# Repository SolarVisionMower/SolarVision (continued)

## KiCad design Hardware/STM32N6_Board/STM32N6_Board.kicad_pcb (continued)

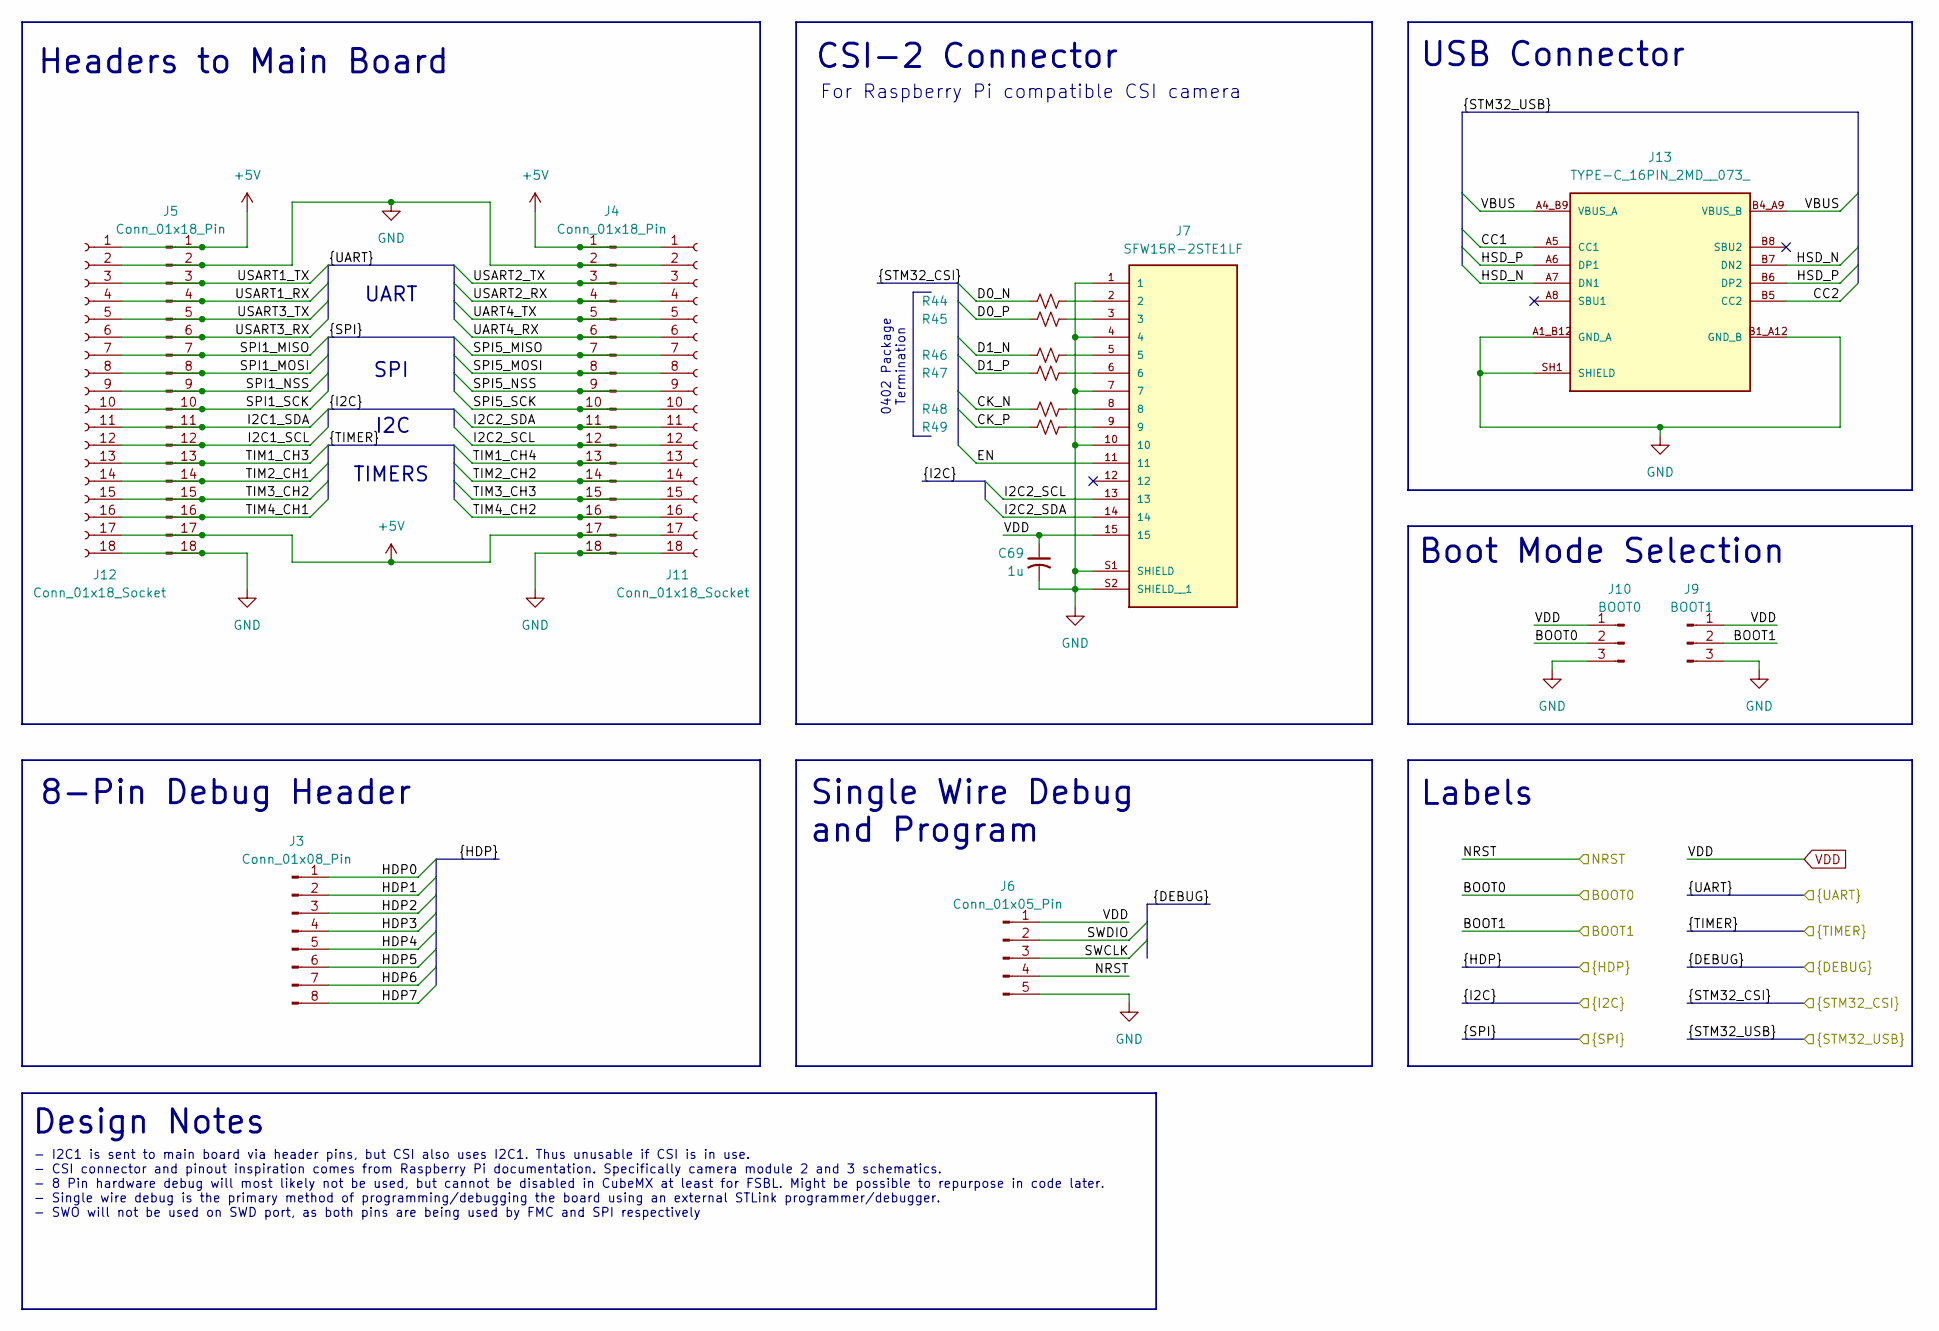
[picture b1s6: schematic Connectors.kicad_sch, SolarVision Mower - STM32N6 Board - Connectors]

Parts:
C69: 1u; C_0805_2012Metric_Pad1.18x1.45mm_HandSolder
J3: Conn_01x08_Pin; PinHeader_1x08_P2.54mm_Vertical
J4, J5: Conn_01x18_Pin; PinHeader_1x18_P2.54mm_Vertical
J6: Conn_01x05_Pin; PinHeader_1x05_P2.54mm_Vertical
J7: SFW15R-2STE1LF; AMPHENOL_SFW15R-2STE1LF; PARTREV AE
J9: BOOT1; PinHeader_1x03_P2.54mm_Vertical
J10: BOOT0; PinHeader_1x03_P2.54mm_Vertical
J11, J12: Conn_01x18_Socket; PinSocket_1x18_P2.54mm_Vertical
J13: TYPE-C_16PIN_2MD__073_; SHOUHAN_TYPE-C_16PIN_2MD__073_; PARTREV A
R44, R45, R46, R47, R48, R49: 0R; R_0402_1005Metric

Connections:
+5V: J4.1, J4.17, J5.1, J5.17, J11.1, J11.17, J12.1, J12.17; also elsewhere on the board
/Analog_Unit/BOOT0: J10.2; also elsewhere on the board
/Analog_Unit/CC1: J13.A5 (CC1); also elsewhere on the board
/Analog_Unit/CC2: J13.B5 (CC2); also elsewhere on the board
/Analog_Unit/CK_N: R48.1; also elsewhere on the board
/Analog_Unit/CK_P: R49.1; also elsewhere on the board
/Analog_Unit/D0_N: R44.1; also elsewhere on the board
/Analog_Unit/D0_P: R45.1; also elsewhere on the board
/Analog_Unit/D1_N: R46.1; also elsewhere on the board
/Analog_Unit/D1_P: R47.1; also elsewhere on the board
/Analog_Unit/EN: J7.11; also elsewhere on the board
/Analog_Unit/HSD_N: J13.A7 (DN1), J13.B7 (DN2); also elsewhere on the board
/Analog_Unit/HSD_P: J13.A6 (DP1), J13.B6 (DP2); also elsewhere on the board
/Analog_Unit/NRST: J6.4; also elsewhere on the board
/Analog_Unit/VBUS: J13.A4_B9 (VBUS_A), J13.B4_A9 (VBUS_B); also elsewhere on the board
/Connectors/BOOT1: J9.2; also elsewhere on the board
/Connectors/HDP0: J3.1; also elsewhere on the board
/Connectors/HDP1: J3.2; also elsewhere on the board
/Connectors/HDP2: J3.3; also elsewhere on the board
/Connectors/HDP3: J3.4; also elsewhere on the board
/Connectors/HDP4: J3.5; also elsewhere on the board
/Connectors/HDP5: J3.6; also elsewhere on the board
/Connectors/HDP6: J3.7; also elsewhere on the board
/Connectors/HDP7: J3.8; also elsewhere on the board
/Connectors/I2C1_SCL: J5.12, J12.12; also elsewhere on the board
/Connectors/I2C1_SDA: J5.11, J12.11; also elsewhere on the board
/Connectors/I2C2_SCL: J4.12, J7.13, J11.12; also elsewhere on the board
/Connectors/I2C2_SDA: J4.11, J7.14, J11.11; also elsewhere on the board
/Connectors/SPI1_MISO: J5.7, J12.7; also elsewhere on the board
/Connectors/SPI1_MOSI: J5.8, J12.8; also elsewhere on the board
/Connectors/SPI1_NSS: J5.9, J12.9; also elsewhere on the board
/Connectors/SPI1_SCK: J5.10, J12.10; also elsewhere on the board
/Connectors/SPI5_MISO: J4.7, J11.7; also elsewhere on the board
/Connectors/SPI5_MOSI: J4.8, J11.8; also elsewhere on the board
/Connectors/SPI5_NSS: J4.9, J11.9; also elsewhere on the board
/Connectors/SPI5_SCK: J4.10, J11.10; also elsewhere on the board
/Connectors/SWCLK: J6.3; also elsewhere on the board
/Connectors/SWDIO: J6.2; also elsewhere on the board
/Connectors/TIM1_CH3: J5.13, J12.13; also elsewhere on the board
/Connectors/TIM1_CH4: J4.13, J11.13; also elsewhere on the board
/Connectors/TIM2_CH1: J5.14, J12.14; also elsewhere on the board
/Connectors/TIM2_CH2: J4.14, J11.14; also elsewhere on the board
/Connectors/TIM3_CH2: J5.15, J12.15; also elsewhere on the board
/Connectors/TIM3_CH3: J4.15, J11.15; also elsewhere on the board
/Connectors/TIM4_CH1: J5.16, J12.16; also elsewhere on the board
/Connectors/TIM4_CH2: J4.16, J11.16; also elsewhere on the board
/Connectors/UART4_RX: J4.6, J11.6; also elsewhere on the board
/Connectors/UART4_TX: J4.5, J11.5; also elsewhere on the board
/Connectors/USART1_RX: J5.4, J12.4; also elsewhere on the board
/Connectors/USART1_TX: J5.3, J12.3; also elsewhere on the board
/Connectors/USART2_RX: J4.4, J11.4; also elsewhere on the board
/Connectors/USART2_TX: J4.3, J11.3; also elsewhere on the board
/Connectors/USART3_RX: J5.6, J12.6; also elsewhere on the board
/Connectors/USART3_TX: J5.5, J12.5; also elsewhere on the board
GND: C69.2, J4.2, J4.18, J5.2, J5.18, J6.5, J7.1, J7.4, J7.7, J7.10, J7.S1 (SHIELD), J7.S2 (SHIELD__1), J9.3, J10.3, J11.2, J11.18, J12.2, J12.18, J13.A1_B12 (GND_A), J13.B1_A12 (GND_B), J13.SH1 (SHIELD), J13.SH2 (SHIELD), J13.SH3 (SHIELD), J13.SH4 (SHIELD); also elsewhere on the board
unnamed: J7.2, R44.2
unnamed: J7.3, R45.2
unnamed: J7.5, R46.2
unnamed: J7.6, R47.2
unnamed: J7.8, R48.2
unnamed: J7.9, R49.2
VDD: C69.1, J6.1, J7.15, J9.1, J10.1; also elsewhere on the board

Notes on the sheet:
Headers to Main Board
CSI-2 Connector
UART
- I2C1 is sent to main board via header pins, but CSI also uses I2C1. Thus unusable if CSI is in use. - CSI connector and pinout inspiration comes from Raspberry Pi documentation. Specifically camera module 2 and 3 schematics. - 8 Pin hardware debug will most likely not be used, but cannot be disab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
Design Notes
Boot Mode Selection
For Raspberry Pi compatible CSI camera
8-Pin Debug Header
SPI
USB Connector
TIMERS
Labels
I2C
0402 Package Termination
Single Wire Debug and Program

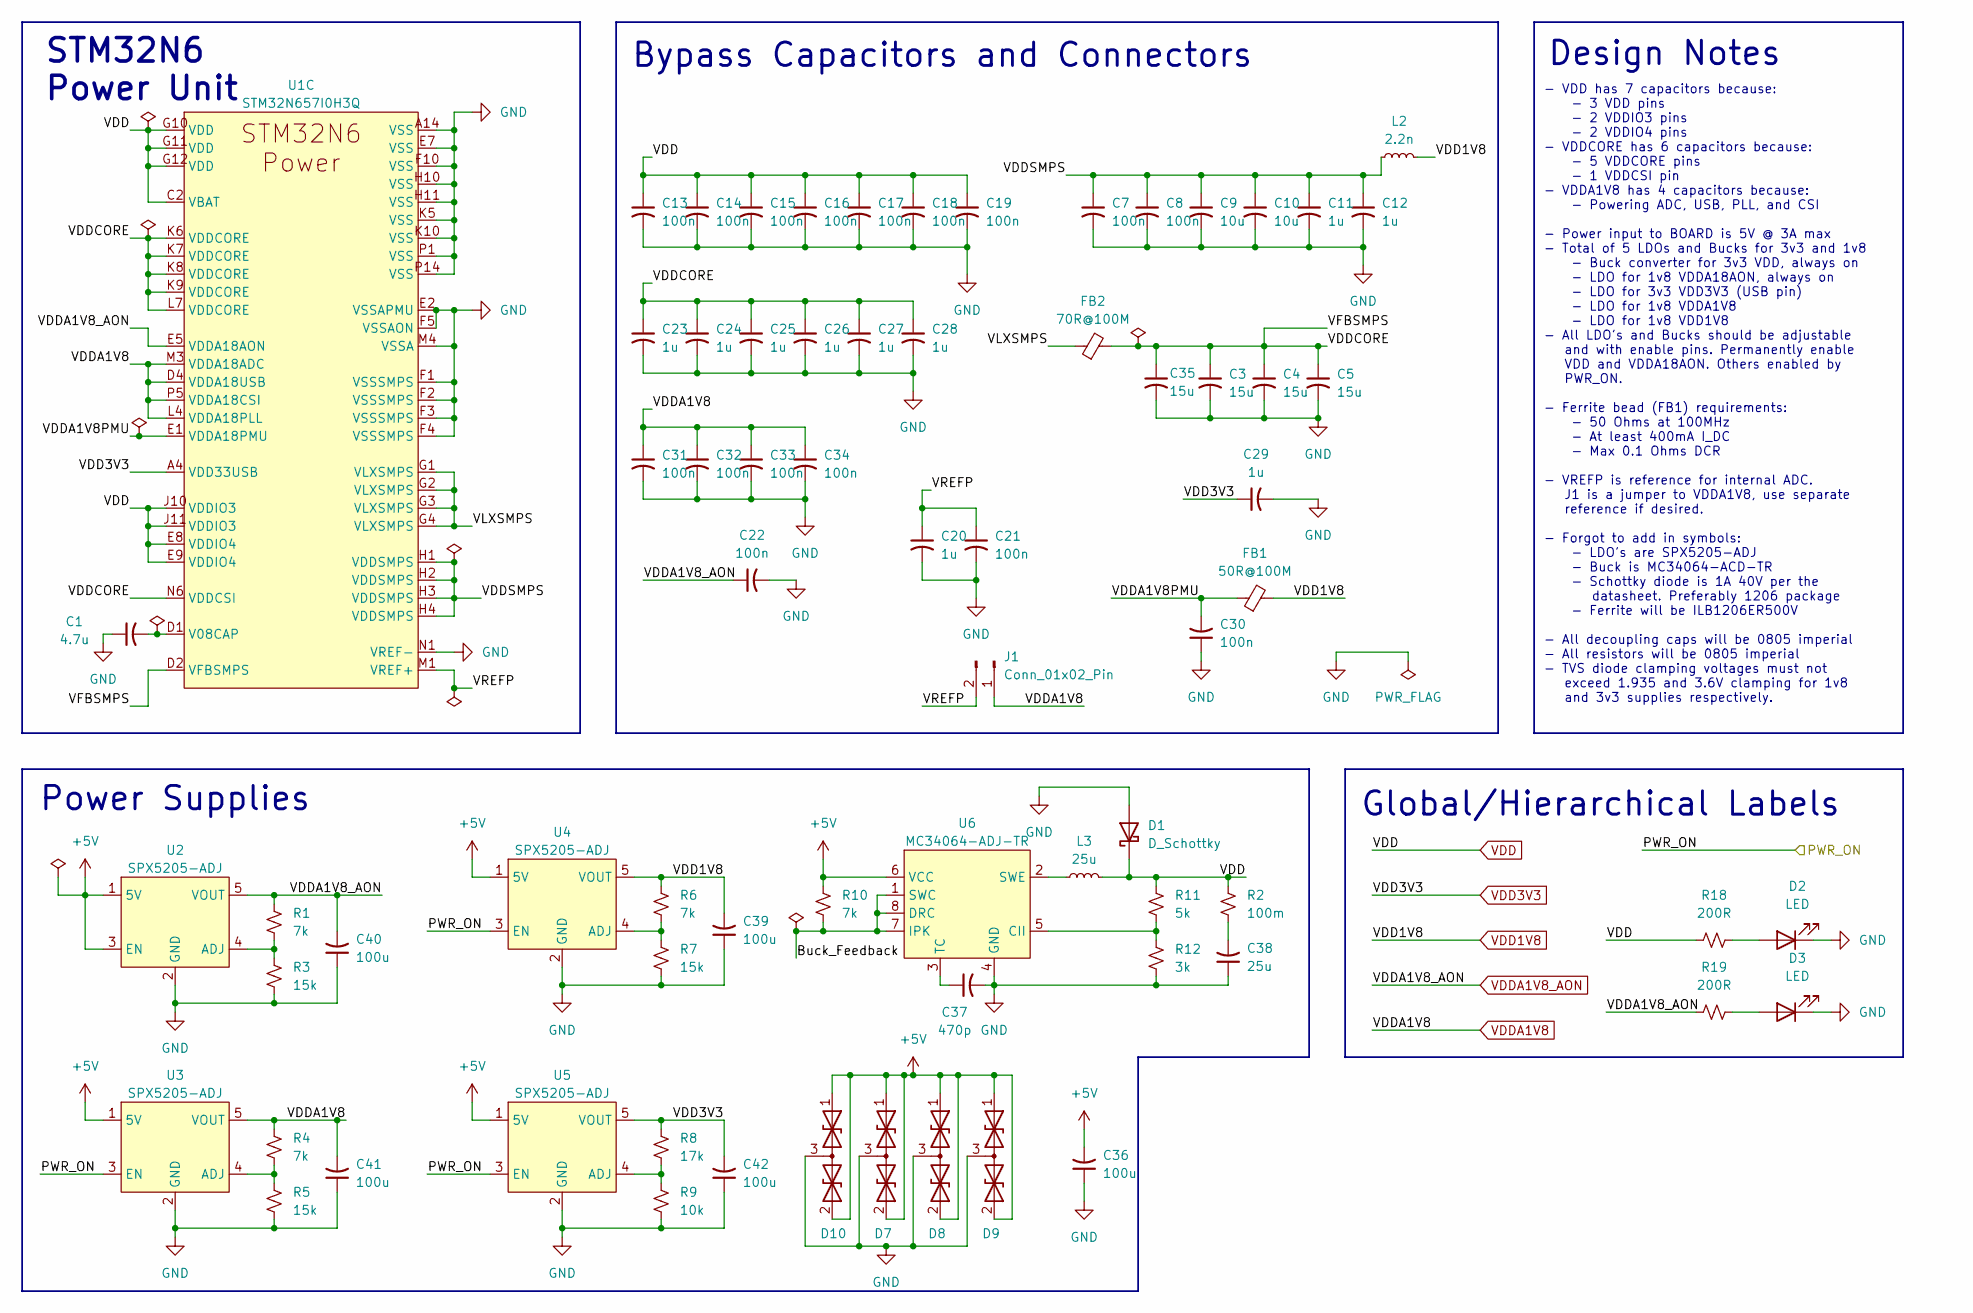
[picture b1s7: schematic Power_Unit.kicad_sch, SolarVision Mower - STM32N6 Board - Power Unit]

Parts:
C1: 4.7u; C_0402_1005Metric
C3, C4, C5, C35: 15u; C_0402_1005Metric
C7, C8, C13, C14, C15, C16, C17, C18, C19, C21, C22, C30, C31, C32, C33, C34: 100n; C_0402_1005Metric
C9, C10: 10u; C_0402_1005Metric
C11, C12, C20, C23, C24, C25, C26, C27, C28: 1u; C_0402_1005Metric
C29: 1u; C_0805_2012Metric_Pad1.18x1.45mm_HandSolder
C36, C39, C40, C41, C42: 100u; C_0805_2012Metric_Pad1.18x1.45mm_HandSolder
C37: 470p; C_0402_1005Metric
C38: 25u; C_0402_1005Metric
D1: D_Schottky; Schottky_DIOM4325X250N
D2, D3: LED; LED_0603_1608Metric_Pad1.05x0.95mm_HandSolder
D7, D8, D9, D10: D_TVS_Dual_AAC; SOT-723
FB1: 50R@100M; L_1206_3216Metric_Pad1.42x1.75mm_HandSolder
FB2: 70R@100M; L_1206_3216Metric_Pad1.42x1.75mm_HandSolder
J1: Conn_01x02_Pin; PinHeader_1x02_P2.54mm_Vertical
L2: 2.2n; L_1206_3216Metric_Pad1.42x1.75mm_HandSolder
L3: 25u; L_1206_3216Metric_Pad1.42x1.75mm_HandSolder
R1, R4, R6, R10: 7k; R_0805_2012Metric_Pad1.20x1.40mm_HandSolder
R2: 100m; R_0805_2012Metric_Pad1.20x1.40mm_HandSolder
R3, R5, R7: 15k; R_0805_2012Metric_Pad1.20x1.40mm_HandSolder
R8: 17k; R_0805_2012Metric_Pad1.20x1.40mm_HandSolder
R9: 10k; R_0805_2012Metric_Pad1.20x1.40mm_HandSolder
R11: 5k; R_0805_2012Metric_Pad1.20x1.40mm_HandSolder
R12: 3k; R_0805_2012Metric_Pad1.20x1.40mm_HandSolder
R18, R19: 200R; R_0402_1005Metric
U1: STM32N657I0H3Q; STM32N657I0H3Q_VFBGA178_14x14
U2, U3, U4, U5: SPX5205-ADJ; SOT-23-5
U6: MC34064-ADJ-TR; SO-8_3.9x4.9mm_P1.27mm

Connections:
+5V: C36.2, D7.1 (A1), D7.2 (A2), D8.1 (A1), D8.2 (A2), D9.1 (A1), D9.2 (A2), D10.1 (A1), D10.2 (A2), R10.1, U2.1 (5V), U2.3 (EN), U3.1 (5V), U4.1 (5V), U5.1 (5V), U6.6 (VCC); also elsewhere on the board
/Analog_Unit/PWR_ON: U3.3 (EN), U4.3 (EN), U5.3 (EN); also elsewhere on the board
/Power_Unit/Buck_Feedback: R10.2, U6.1 (SWC), U6.7 (IPK), U6.8 (DRC)
/Power_Unit/VDDA1V8PMU: C30.2, FB1.1, U1.E1 (VDDA18PMU)
/Power_Unit/VDDCORE: C3.1, C4.1, C5.1, C23.1, C24.1, C25.1, C26.1, C27.1, C28.1, C35.1, FB2.2, U1.D2 (VFBSMPS), U1.K6 (VDDCORE), U1.K7 (VDDCORE), U1.K8 (VDDCORE), U1.K9 (VDDCORE), U1.L7 (VDDCORE), U1.N6 (VDDCSI)
/Power_Unit/VDDSMPS: C7.1, C8.1, C9.1, C10.1, C11.1, C12.1, L2.1, U1.H1 (VDDSMPS), U1.H2 (VDDSMPS), U1.H3 (VDDSMPS), U1.H4 (VDDSMPS)
/Power_Unit/VLXSMPS: FB2.1, U1.G1 (VLXSMPS), U1.G2 (VLXSMPS), U1.G3 (VLXSMPS), U1.G4 (VLXSMPS)
/Power_Unit/VREFP: C20.1, C21.1, J1.2, U1.M1 (VREF+)
GND: C1.1, C3.2, C4.2, C5.2, C7.2, C8.2, C9.2, C10.2, C11.2, C12.2, C13.2, C14.2, C15.2, C16.2, C17.2, C18.2, C19.2, C20.2, C21.2, C22.2, C23.2, C24.2, C25.2, C26.2, C27.2, C28.2, C29.2, C30.1, C31.2, C32.2, C33.2, C34.2, C35.2, C36.1, C37.2, C38.1, C39.1, C40.1, C41.1, C42.1, D1.2 (A), D2.1 (K), D3.1 (K), D7.3 (common), D8.3 (common), D9.3 (common), D10.3 (common), R3.2, R5.2, R7.2, R9.2, R12.2, U1.A14 (VSS), U1.E2 (VSSAPMU), U1.E7 (VSS), U1.F1 (VSSSMPS), U1.F2 (VSSSMPS), U1.F3 (VSSSMPS), U1.F4 (VSSSMPS), U1.F5 (VSSAON), U1.F10 (VSS), U1.H10 (VSS), U1.H11 (VSS), U1.K5 (VSS), U1.K10 (VSS), U1.M4 (VSSA), U1.N1 (VREF-), U1.P1 (VSS), U1.P14 (VSS), U2.2 (GND), U3.2 (GND), U4.2 (GND), U5.2 (GND), U6.4 (GND); also elsewhere on the board
unnamed: D2.2 (A), R18.2
unnamed: D3.2 (A), R19.2
unnamed: C1.2, U1.D1 (V08CAP)
unnamed: R1.2, R3.1, U2.4 (ADJ)
unnamed: R4.2, R5.1, U3.4 (ADJ)
unnamed: R6.2, R7.1, U4.4 (ADJ)
unnamed: R8.2, R9.1, U5.4 (ADJ)
unnamed: R11.2, R12.1, U6.5 (CII)
unnamed: L3.1, U6.2 (SWE)
unnamed: C37.1, U6.3 (TC)
VDD: C13.1, C14.1, C15.1, C16.1, C17.1, C18.1, C19.1, C38.2, D1.1 (K), L3.2, R2.1, R2.2, R11.1, R18.1, U1.C2 (VBAT), U1.E8 (VDDIO4), U1.E9 (VDDIO4), U1.G10 (VDD), U1.G11 (VDD), U1.G12 (VDD), U1.J10 (VDDIO3), U1.J11 (VDDIO3); also elsewhere on the board
VDD1V8: C39.2, FB1.2, L2.2, R6.1, U4.5 (VOUT)
VDD3V3: C29.1, C42.2, R8.1, U1.A4 (VDD33USB), U5.5 (VOUT); also elsewhere on the board
VDDA1V8: C31.1, C32.1, C33.1, C34.1, C41.2, J1.1, R4.1, U1.D4 (VDDA18USB), U1.L4 (VDDA18PLL), U1.M3 (VDDA18ADC), U1.P5 (VDDA18CSI), U3.5 (VOUT)
VDDA1V8_AON: C22.1, C40.2, R1.1, R19.1, U1.E5 (VDDA18AON), U2.5 (VOUT); also elsewhere on the board

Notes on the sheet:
Global/Hierarchical Labels
Bypass Capacitors and Connectors
- VDD has 7 capacitors because: - 3 VDD pins - 2 VDDIO3 pins - 2 VDDIO4 pins - VDDCORE has 6 capacitors because: - 5 VDDCORE pins - 1 VDDCSI pin - VDDA1V8 has 4 capacitors because: - Powering ADC, USB, PLL, and CSI - Power input to BOARD is 5V @ 3A max - Total of 5 LDOs and Bucks for 3v3 and 1v8 - 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
Design Notes
STM32N6 Power Unit
Power Supplies

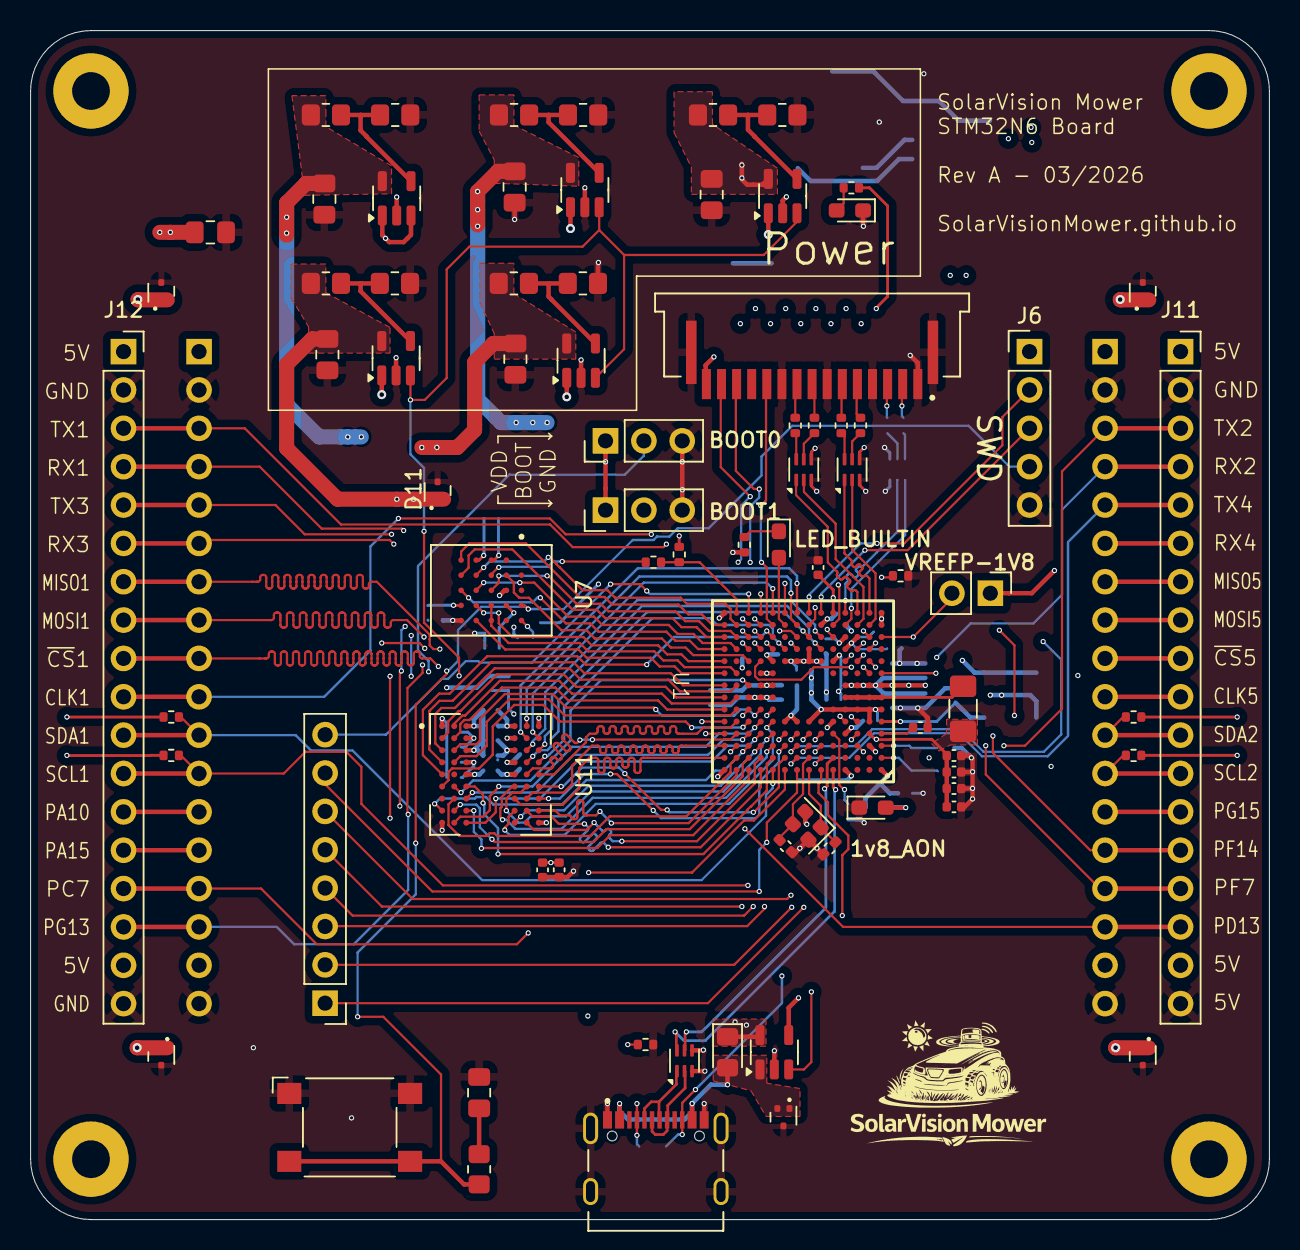
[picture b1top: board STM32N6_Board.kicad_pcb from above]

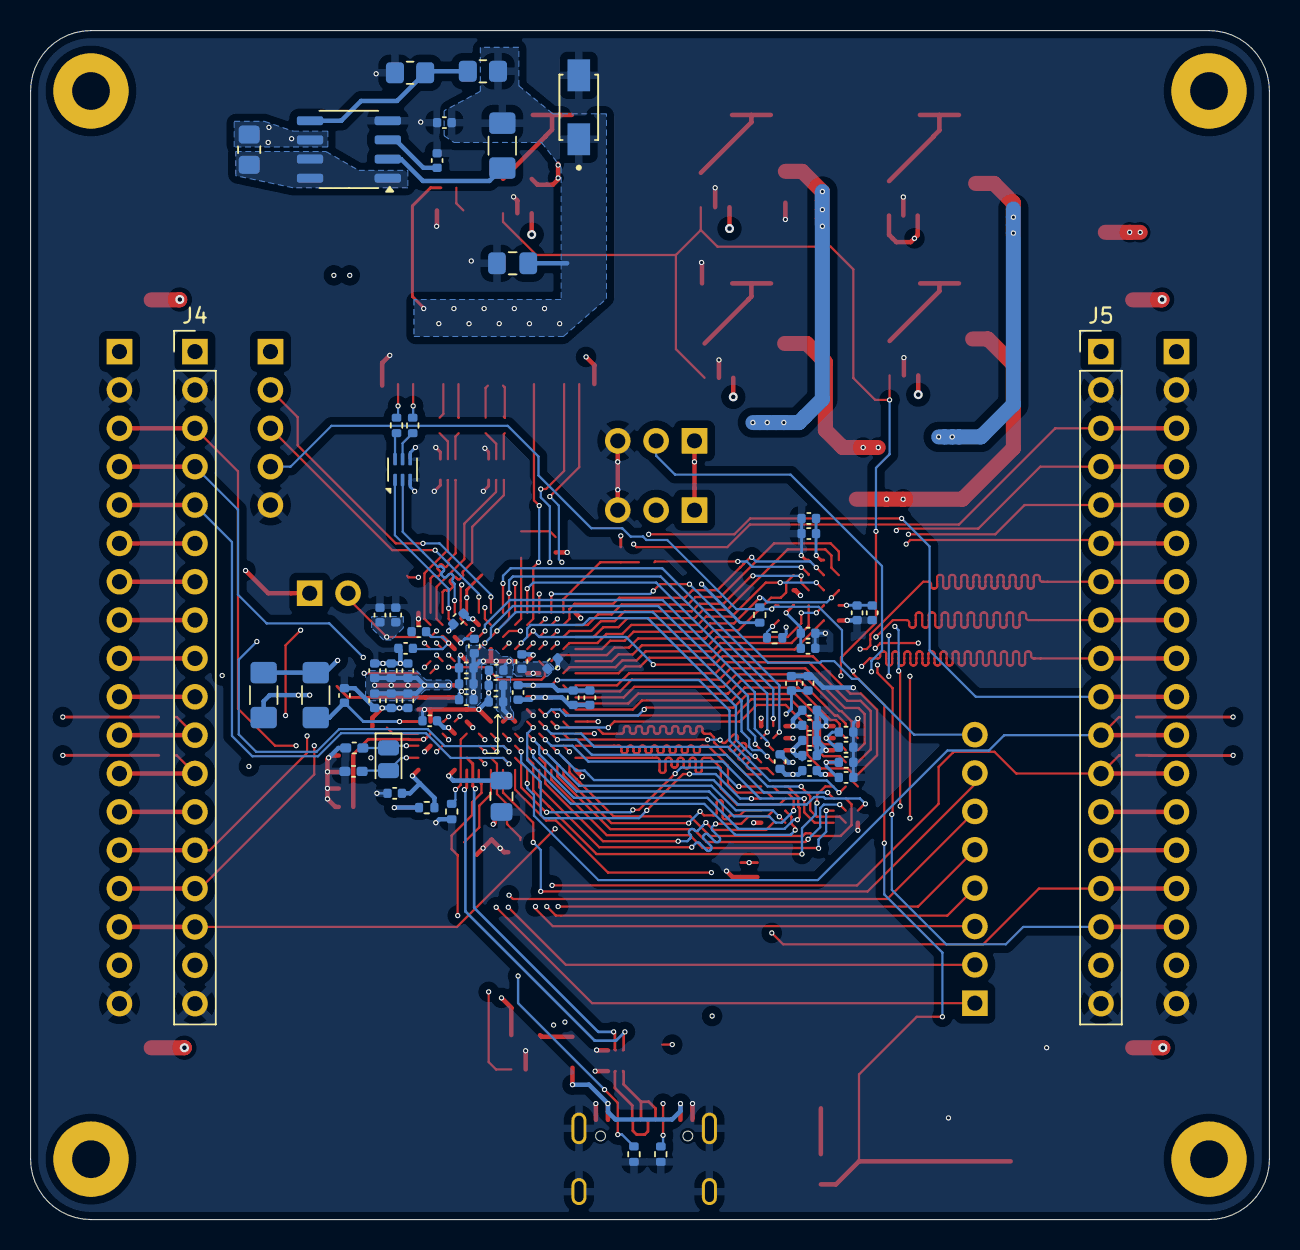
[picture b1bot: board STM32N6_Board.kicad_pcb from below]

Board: 6 copper layers, 82.0 x 78.7 mm, 146 parts (70 on the bottom side), 155 nets.

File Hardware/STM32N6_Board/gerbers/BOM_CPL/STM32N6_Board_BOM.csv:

"Id";"Designator";"Footprint";"Quantity";"Designation";"Supplier and ref";
1;"R31";"R_0402_1005Metric";1;"200";;;
2;"C42,C39,C41,C50,C40,C36";"C_0805_2012Metric_Pad1.18x1.45mm_HandSolder";6;"100u";;;
3;"U8,U2,U4,U5,U3";"SOT-23-5";5;"SPX5205-ADJ";;;
4;"C54,C53,C52,C49";"C_0402_1005Metric_Pad0.74x0.62mm_HandSolder";4;"12p";;;
5;"D8,D10,D9,D7";"SOT-723";4;"D_TVS_Dual_AAC";;;
6;"D4,D12";"LED_0805_2012Metric_Pad1.15x1.40mm_HandSolder";2;"D_TVS";;;
7;"R9,R27,R22";"R_0805_2012Metric_Pad1.20x1.40mm_HandSolder";3;"10k";;;
8;"C56,C32,C22,C14,C33,C60,C13,C62,C48,C64,C30,C21,C16,C66,C34,C7,C31,C18,C68,C43,C8,C46,C15,C58,C19,C17";"C_0402_1005Metric";26;"100n";;;
9;"C57,C1,C63,C47,C44,C45,C55,C59,C67,C65,C61";"C_0402_1005Metric";11;"4.7u";;;
10;"R15,R29,R30,R28";"R_0402_1005Metric";4;"2k";;;
11;"J10";"PinHeader_1x03_P2.54mm_Vertical";1;"BOOT0";;;
12;"R46,R49,R47,R48,R13,R45,R44";"R_0402_1005Metric";7;"0R";;;
13;"R21,R3,R7,R5";"R_0805_2012Metric_Pad1.20x1.40mm_HandSolder";4;"15k";;;
14;"FB2";"L_1206_3216Metric_Pad1.42x1.75mm_HandSolder";1;"70R@100M";;;
15;"J12,J11";"PinSocket_1x18_P2.54mm_Vertical";2;"Conn_01x18_Socket";;;
16;"C4,C3,C5,C35";"C_0402_1005Metric";4;"15u";;;
17;"R16,R26,R14,R17";"R_0402_1005Metric";4;"10k";;;
18;"J9";"PinHeader_1x03_P2.54mm_Vertical";1;"BOOT1";;;
19;"U10";"SOT-23-5";1;"STMPS2151STR";;;
20;"R8";"R_0805_2012Metric_Pad1.20x1.40mm_HandSolder";1;"17k";;;
21;"J6";"PinHeader_1x05_P2.54mm_Vertical";1;"Conn_01x05_Pin";;;
22;"U14,U12,U9,U13";"ST_UQFN-6L_1.5x1.7mm_P0.5mm";4;"ECMF2-40A100N6";;;
23;"R4,R1,R6,R10";"R_0805_2012Metric_Pad1.20x1.40mm_HandSolder";4;"7k";;;
24;"D2,D3";"LED_0603_1608Metric_Pad1.05x0.95mm_HandSolder";2;"LED";;;
25;"J1";"PinHeader_1x02_P2.54mm_Vertical";1;"Conn_01x02_Pin";;;
26;"C51";"C_0805_2012Metric_Pad1.18x1.45mm_HandSolder";1;"100n";;;
27;"U11";"IS42S16800F-7BL_BGA54C80P9X9_800X800X120";1;"IS42S16800F-7BL";;;
28;"R20";"R_0402_1005Metric";1;"20R";;;
29;"D5";"LED_0805_2012Metric_Pad1.15x1.40mm_HandSolder";1;"D";;;
30;"J3";"PinHeader_1x08_P2.54mm_Vertical";1;"Conn_01x08_Pin";;;
31;"Y3";"48MHz_Q22FA12800150_4Pin_2.0z1.6mm";1;"48MHz";;;
32;"J7";"AMPHENOL_SFW15R-2STE1LF";1;"SFW15R-2STE1LF";;;
33;"U1";"STM32N657I0H3Q_VFBGA178_14x14";1;"STM32N657I0H3Q";;;
34;"SW2";"SW_SPST_Omron_B3FS-101xP";1;"SW_Push";;;
35;"J13";"SHOUHAN_TYPE-C_16PIN_2MD__073_";1;"TYPE-C_16PIN_2MD__073_";;;
36;"D6";"LED_0603_1608Metric_Pad1.05x0.95mm_HandSolder";1;"LED_Small";;;
37;"R18,R19,R23";"R_0402_1005Metric";3;"200R";;;
38;"U7";"MX25LM51245GXD100_BGA24C100P5X5_600X800X120";1;"MX25LM51245GXDI00";;;
39;"FB1";"L_1206_3216Metric_Pad1.42x1.75mm_HandSolder";1;"50R@100M";;;
40;"R11";"R_0805_2012Metric_Pad1.20x1.40mm_HandSolder";1;"5k";;;
41;"J5,J4";"PinHeader_1x18_P2.54mm_Vertical";2;"Conn_01x18_Pin";;;
42;"Y1";"32kHz_SC-20S_2Pin_2.05x1.2mm";1;"32.768kHz";;;
43;"C37";"C_0402_1005Metric";1;"470p";;;
44;"C28,C26,C12,C25,C11,C23,C24,C27,C20";"C_0402_1005Metric";9;"1u";;;
45;"C69,C29";"C_0805_2012Metric_Pad1.18x1.45mm_HandSolder";2;"1u";;;
46;"L3";"L_1206_3216Metric_Pad1.42x1.75mm_HandSolder";1;"220u";;;
47;"C38";"C_0402_1005Metric";1;"470u";;;
48;"R25,R24";"R_0402_1005Metric";2;"5k";;;
49;"L2";"L_1206_3216Metric_Pad1.42x1.75mm_HandSolder";1;"2.2n";;;
50;"D1";"Schottky_DIOM4325X250N";1;"D_Schottky";;;
51;"C9,C10";"C_0402_1005Metric";2;"10u";;;
52;"U6";"SO-8_3.9x4.9mm_P1.27mm";1;"MC34064-ADJ-TR";;;
53;"R12";"R_0805_2012Metric_Pad1.20x1.40mm_HandSolder";1;"3k";;;

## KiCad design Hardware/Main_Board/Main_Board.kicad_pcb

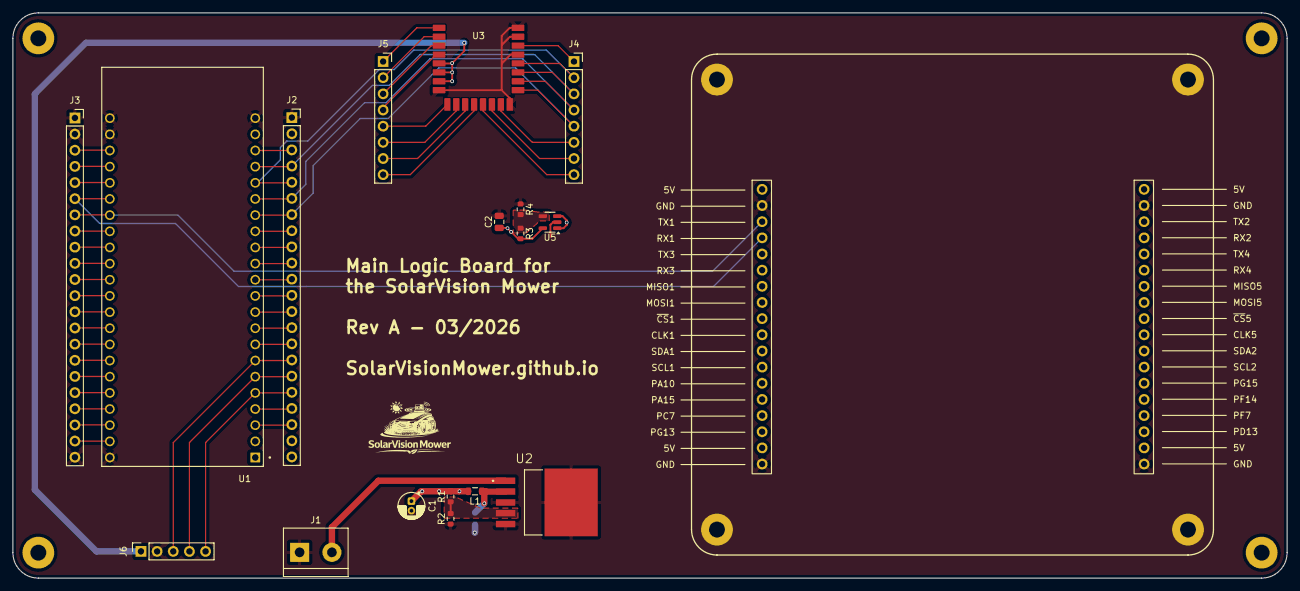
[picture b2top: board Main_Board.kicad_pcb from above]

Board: 2 copper layers, 200.3 x 88.8 mm, 19 parts (1 on the bottom side), 56 nets.

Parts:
C1: 220u; CP_Radial_D4.0mm_P1.50mm
C2: 100u; C_0805_2012Metric
D1: D_Schottky; C_0805_2012Metric
J1: Conn_01x02_Socket; TerminalBlock_bornier-2_P5.08mm
J2, J3: Conn_01x22_Socket; PinSocket_1x22_P2.54mm_Vertical
J4, J5: Conn_01x08_Socket; PinSocket_1x08_P2.54mm_Vertical
J6: Conn_01x05_Socket; PinSocket_1x05_P2.54mm_Vertical
L1: 68u; L_0805_2012Metric
R1: 3k; R_0603_1608Metric
R2: 1k; R_0603_1608Metric
R3: 17k; R_0603_1608Metric
R4: 10k; R_0603_1608Metric
U1: ESP32-S3-DEVKITC-1U-N8R2; XCVR_ESP32-S3-DEVKITC-1U-N8R2
U2: LM2596DSADJG; CONV_LM2596DSADJG
U3: DWM1000; BU01
U4: STM32N6_Board
U5: SOT-23-5

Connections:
5V0: C1.1, J2.2, L1.2, R1.2, U1.J1_21 (5V0), U4.1 (5V), U4.17 (5V), U4.20 (5V), U4.36 (5V), U5.1 (5V), U5.3 (EN)
+BATT: J1.2, U2.1 (VIN)
/Connectors/EXTON: J5.1, U3.1 (EXTON)
/Connectors/GPIO0: J3.9, U1.J3_14 (GPIO0)
/Connectors/GPIO1: J3.19, U1.J3_4 (GPIO1)
/Connectors/GPIO2: J3.18, U1.J3_5 (GPIO2)
/Connectors/GPIO3: J2.10, U1.J1_13 (GPIO3)
/Connectors/GPIO4: J2.19, U1.J1_4 (GPIO4)
/Connectors/GPIO5: J2.18, J6.5, U1.J1_5 (GPIO5)
/Connectors/GPIO6: J2.17, J6.4, U1.J1_6 (GPIO6)
/Connectors/GPIO7: J2.16, J6.3, U1.J1_7 (GPIO7)
/Connectors/GPIO8: J2.11, U1.J1_12 (GPIO8)
/Connectors/GPIO9: J2.8, U1.J1_15 (GPIO9)
/Connectors/GPIO10: J2.7, J4.5, U1.J1_16 (GPIO10), U3.17 (SPICSN)
/Connectors/GPIO11: J2.6, J4.4, U1.J1_17 (GPIO11), U3.18 (SPIMOSI)
/Connectors/GPIO12: J2.5, J4.2, U1.J1_18 (GPIO12), U3.20 (SPICLK)
/Connectors/GPIO13: J2.4, J4.3, U1.J1_19 (GPIO13), U3.19 (SPIMISO)
/Connectors/GPIO14: J2.3, U1.J1_20 (GPIO14)
/Connectors/GPIO15: J2.15, U1.J1_8 (GPIO15)
/Connectors/GPIO16: J2.14, U1.J1_9 (GPIO16)
/Connectors/GPIO17: J2.13, U1.J1_10 (GPIO17)
/Connectors/GPIO18: J2.12, U1.J1_11 (GPIO18)
/Connectors/GPIO19: J3.3, U1.J3_20 (USB_D-/GPIO19)
/Connectors/GPIO20: J3.4, U1.J3_19 (USB_D+/GPIO20)
/Connectors/GPIO21: J3.5, U1.J3_18 (GPIO21)
/Connectors/GPIO35: J3.10, U1.J3_13 (GPIO35)
/Connectors/GPIO36: J3.11, U1.J3_12 (GPIO36)
/Connectors/GPIO37: J3.12, U1.J3_11 (GPIO37)
/Connectors/GPIO38: J3.13, U1.J3_10 (GPIO38)
/Connectors/GPIO39: J3.14, U1.J3_9 (MTCK/GPIO39)
/Connectors/GPIO40: J3.15, U1.J3_8 (MTDO/GPIO40)
/Connectors/GPIO41: J3.16, U1.J3_7 (MTDI/GPIO41)
/Connectors/GPIO42: J3.17, U1.J3_6 (MTMS/GPIO42)
/Connectors/GPIO43: J3.21, U1.J3_2 (U0TXD/GPIO43)
/Connectors/GPIO44: J3.20, U1.J3_3 (U0RXD/GPIO44)
/Connectors/GPIO45: J3.8, U1.J3_15 (GPIO45)
/Connectors/GPIO46: J2.9, U1.J1_14 (GPIO46)
/Connectors/IRQ: J4.1, U3.22 (IRQ/GPIO8)
/Connectors/RST: J2.20, U1.J1_3 (RST)
/Connectors/RX1: J3.6, U1.J3_17 (GPIO47), U4.4 (RX1)
/Connectors/TX1: J3.7, U1.J3_16 (GPIO48), U4.3 (TX1)
/Connectors/WAKEUP: J5.2, U3.2 (WAKEUP)
/Connectors/uGPIO0: J4.6, U3.15 (GPIO0)
/Connectors/uGPIO1: J4.7, U3.14 (GPIO1)
/Connectors/uGPIO2: J4.8, U3.13 (GPIO2)
/Connectors/uGPIO3: J5.8, U3.12 (GPIO3)
/Connectors/uGPIO4: J5.7, U3.11 (GPIO4)
/Connectors/uGPIO5: J5.6, U3.10 (GPIO5)
/Connectors/uGPIO6: J5.5, U3.9 (GPIO6)
/Connectors/uGPIO7: J5.4, U3.4 (GPIO7)
/Connectors/~RST: J5.3, U3.3 (RSTN)
GND: C1.2, C2.2, D1.2 (A), J1.1, J2.1, J3.1, J3.2, J3.22, J6.2, R2.1, R4.1, U1.J1_22 (GND), U1.J3_1 (GND), U1.J3_21 (GND), U1.J3_22 (GND), U2.3 (GROUND), U2.5 (~ON/OFF), U2.6 (EXP), U3.8 (VSS@1), U3.16 (VSS@2), U3.21 (VSS@3), U3.23 (VSS@4), U3.24 (VSS@5), U4.2 (GND), U4.18 (GND), U4.19 (GND), U4.35 (GND), U4.GND1 (GND), U4.GND2 (GND), U4.GND3 (GND), U4.GND4 (GND), U5.2 (GND)
unnamed: D1.1 (K), L1.1, U2.2 (OUTPUT)
unnamed: R1.1, R2.2, U2.4 (FEEDBACK)
unnamed: R3.1, R4.2, U5.4 (ADJ)
VDD3V3: C2.1, J6.1, R3.2, U1.J1_1 (3V3), U1.J1_2 (3V3), U3.5 (VDDAON), U3.6 (VDD3V3@1), U3.7 (VDD3V3@2), U5.5 (VOUT)

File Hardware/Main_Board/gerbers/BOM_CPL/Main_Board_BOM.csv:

"Id";"Designator";"Footprint";"Quantity";"Designation";"Supplier and ref";
1;"L1";"L_0805_2012Metric";1;"68u";;;
2;"J5,J4";"PinSocket_1x08_P2.54mm_Vertical";2;"Conn_01x08_Socket";;;
3;"J2,J3";"PinSocket_1x22_P2.54mm_Vertical";2;"Conn_01x22_Socket";;;
4;"D1";"C_0805_2012Metric";1;"D_Schottky";;;
5;"J6";"PinSocket_1x05_P2.54mm_Vertical";1;"Conn_01x05_Socket";;;
6;"U2";"CONV_LM2596DSADJG";1;"LM2596DSADJG";;;
7;"J1";"TerminalBlock_bornier-2_P5.08mm";1;"Conn_01x02_Socket";;;
8;"C1";"CP_Radial_D4.0mm_P1.50mm";1;"220u";;;
9;"U4";"STM32N6_Board";1;"~";;;
10;"C2";"C_0805_2012Metric";1;"100u";;;
11;"R2";"R_0603_1608Metric";1;"1k";;;
12;"U1";"XCVR_ESP32-S3-DEVKITC-1U-N8R2";1;"ESP32-S3-DEVKITC-1U-N8R2";;;
13;"U5";"SOT-23-5";1;"~";;;
14;"R4";"R_0603_1608Metric";1;"10k";;;
15;"R1";"R_0603_1608Metric";1;"3k";;;
16;"R3";"R_0603_1608Metric";1;"17k";;;
17;"U3";"BU01";1;"DWM1000";;;

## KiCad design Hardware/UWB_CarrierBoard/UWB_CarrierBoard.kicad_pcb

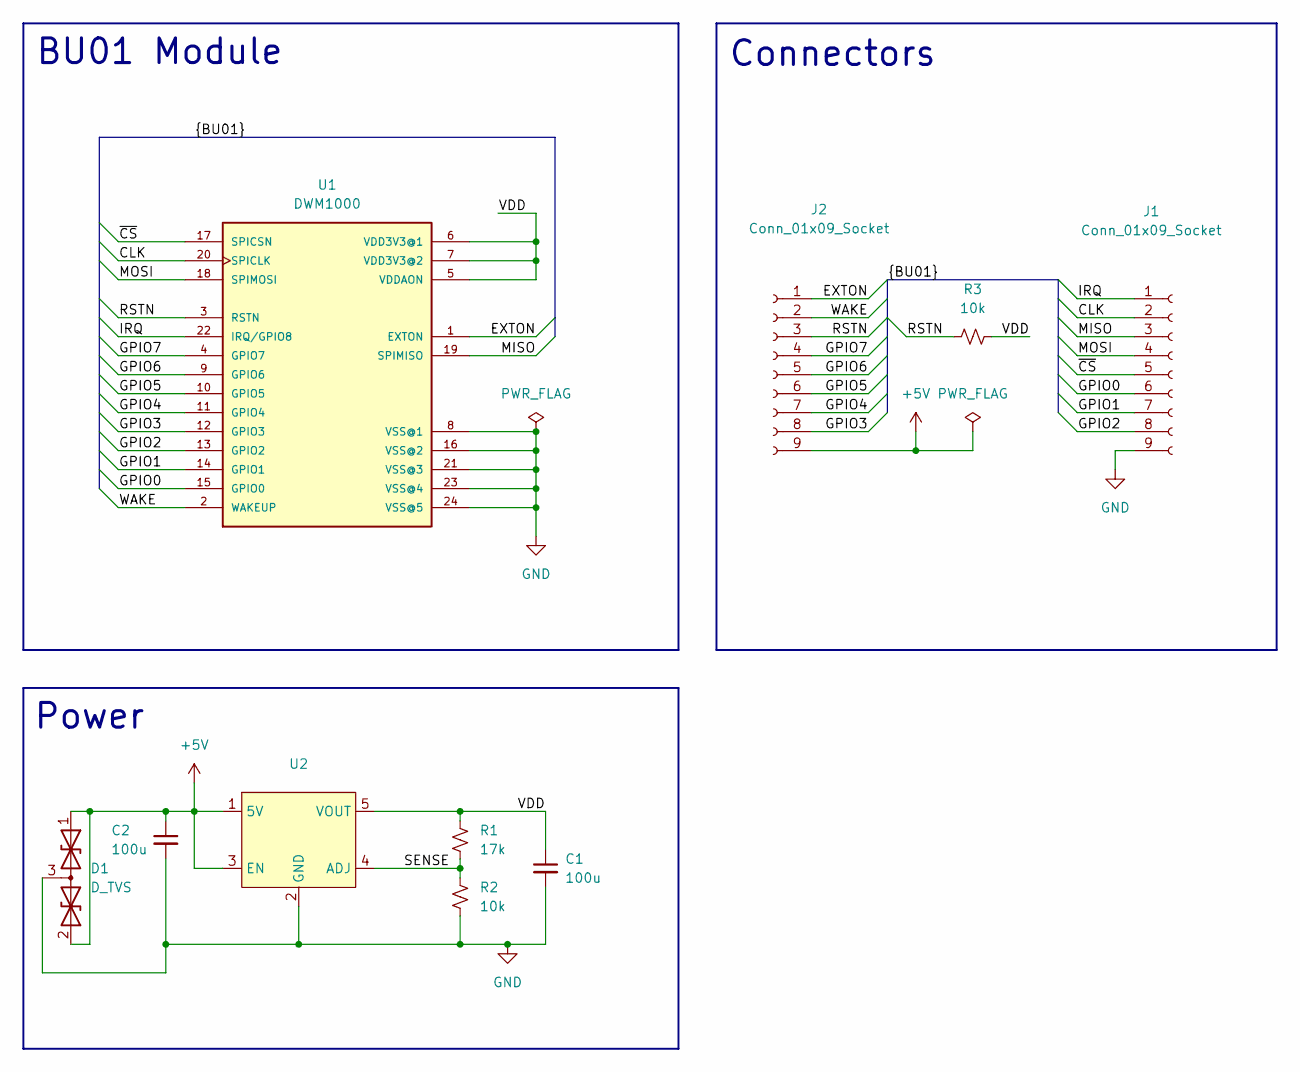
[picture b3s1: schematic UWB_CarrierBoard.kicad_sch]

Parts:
C1, C2: 100u; C_0402_1005Metric
D1: D_TVS; SOT-723
J1, J2: Conn_01x09_Socket; PinSocket_1x09_P2.54mm_Vertical
R1: 17k; R_0402_1005Metric
R2, R3: 10k; R_0402_1005Metric
U1: DWM1000; BU01
U2: SOT-23-5

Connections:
+5V: C2.1, D1.1 (A1), D1.2 (A2), J2.9, U2.1 (5V), U2.3 (EN)
/CLK: J1.2, U1.20 (SPICLK)
/EXTON: J2.1, U1.1 (EXTON)
/GPIO0: J1.6, U1.15 (GPIO0)
/GPIO1: J1.7, U1.14 (GPIO1)
/GPIO2: J1.8, U1.13 (GPIO2)
/GPIO3: J2.8, U1.12 (GPIO3)
/GPIO4: J2.7, U1.11 (GPIO4)
/GPIO5: J2.6, U1.10 (GPIO5)
/GPIO6: J2.5, U1.9 (GPIO6)
/GPIO7: J2.4, U1.4 (GPIO7)
/IRQ: J1.1, U1.22 (IRQ/GPIO8)
/MISO: J1.3, U1.19 (SPIMISO)
/MOSI: J1.4, U1.18 (SPIMOSI)
/RSTN: J2.3, R3.1, U1.3 (RSTN)
/SENSE: R1.2, R2.1, U2.4 (ADJ)
/VDD: C1.1, R1.1, R3.2, U1.5 (VDDAON), U1.6 (VDD3V3@1), U1.7 (VDD3V3@2), U2.5 (VOUT)
/WAKE: J2.2, U1.2 (WAKEUP)
/~CS: J1.5, U1.17 (SPICSN)
GND: C1.2, C2.2, D1.3 (common), J1.9, R2.2, U1.8 (VSS@1), U1.16 (VSS@2), U1.21 (VSS@3), U1.23 (VSS@4), U1.24 (VSS@5), U2.2 (GND)

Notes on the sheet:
Connectors
BU01 Module
Power

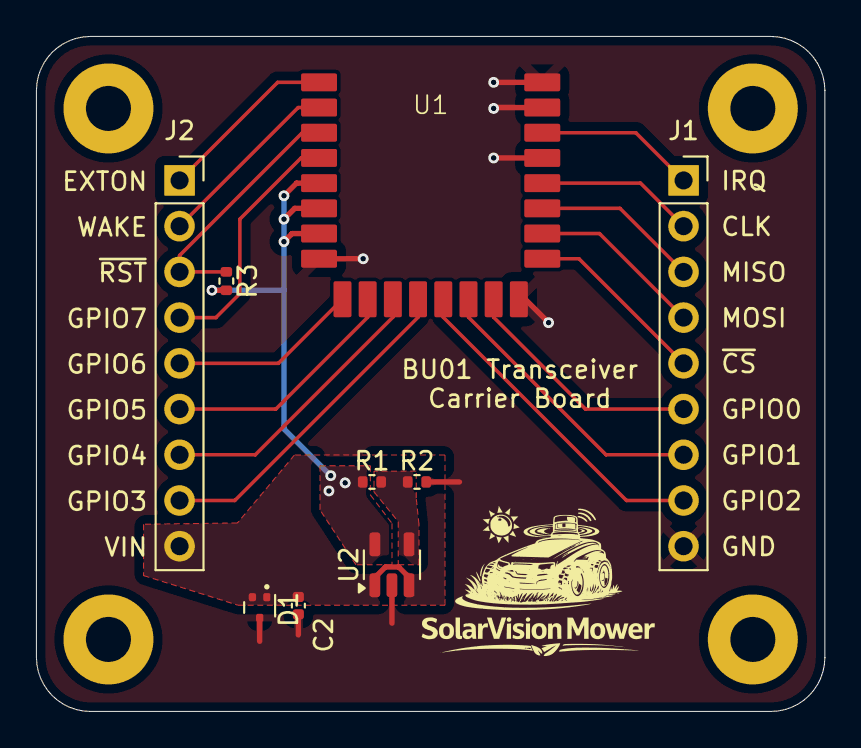
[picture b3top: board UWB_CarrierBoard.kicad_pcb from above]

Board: 2 copper layers, 43.8 x 37.5 mm, 10 parts (1 on the bottom side), 20 nets.

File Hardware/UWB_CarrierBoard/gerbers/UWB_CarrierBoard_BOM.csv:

Comment,Designator,Footprint,JLCPCB Part #
D_TVS,D2,D_0805_2012Metric,C233435
Conn_01x09_Socket,"J2,J1",PinSocket_1x09_P2.54mm_Vertical,C2897372
10k,"R2,R3",R_0402_1005Metric,C25531
17k,R1,R_0402_1005Metric,C25542
100u,"C2,C1",C_0402_1005Metric,C88945
SPX5205,U2,SOT-23-5,C6863
